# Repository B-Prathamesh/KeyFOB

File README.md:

# KeyFOB
Multipurpose keychain with Microcontroller

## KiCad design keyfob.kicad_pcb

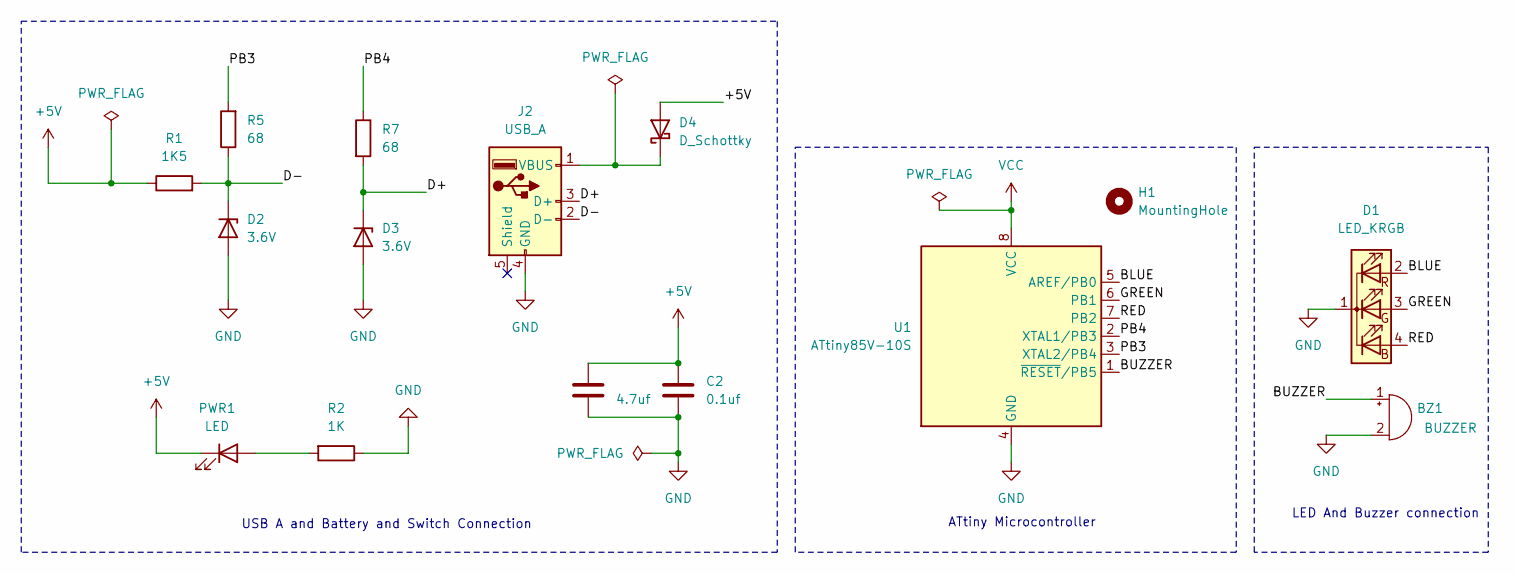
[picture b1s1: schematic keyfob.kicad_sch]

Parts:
BZ1: BUZZER; Buzzer_15x7.5RM7.6
C1: 4.7uf; C_Elec_3x5.4
C2: 0.1uf; C_Elec_3x5.4
D1: LED_KRGB; LED_RGB_1210
D2, D3: 3.6V; D_0805_2012Metric
D4: D_Schottky; D_0805_2012Metric
H1: MountingHole; MountingHole_4mm
J2: USB_A; USB_A_Molex_67643_Horizontal
PWR1: LED; LED_0805_2012Metric
R1: 1K5; R_0805_2012Metric
R2: 1K; R_0805_2012Metric
R5, R7: 68; R_0805_2012Metric
U1: ATtiny85V-10S; SOIC-8W_5.3x5.3mm_P1.27mm

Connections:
+5V: C1.1, C2.1, D4.2 (A), PWR1.1 (K), R1.1
/BLUE: D1.2 (RA), U1.5 (AREF/PB0)
/BUZZER: BZ1.1 (+), U1.1 (~RESET/PB5)
/D+: D3.1 (K), J2.3 (D+), R7.2
/D-: D2.1 (K), J2.2 (D-), R1.2, R5.1
/GREEN: D1.3 (GA), U1.6 (PB1)
/PB3: R5.2, U1.3 (XTAL2/PB4)
/PB4: R7.1, U1.2 (XTAL1/PB3)
/RED: D1.4 (BA), U1.7 (PB2)
GND: BZ1.2 (-), C1.2, C2.2, D1.1 (K), D2.2 (A), D3.2 (A), J2.4 (GND), R2.1, U1.4 (GND)
unnamed: D4.1 (K), J2.1 (VBUS)
unnamed: PWR1.2 (A), R2.2
VCC: U1.8 (VCC)

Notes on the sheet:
LED And Buzzer connection
USB A and Battery and Switch Connection
ATtiny Microcontroller

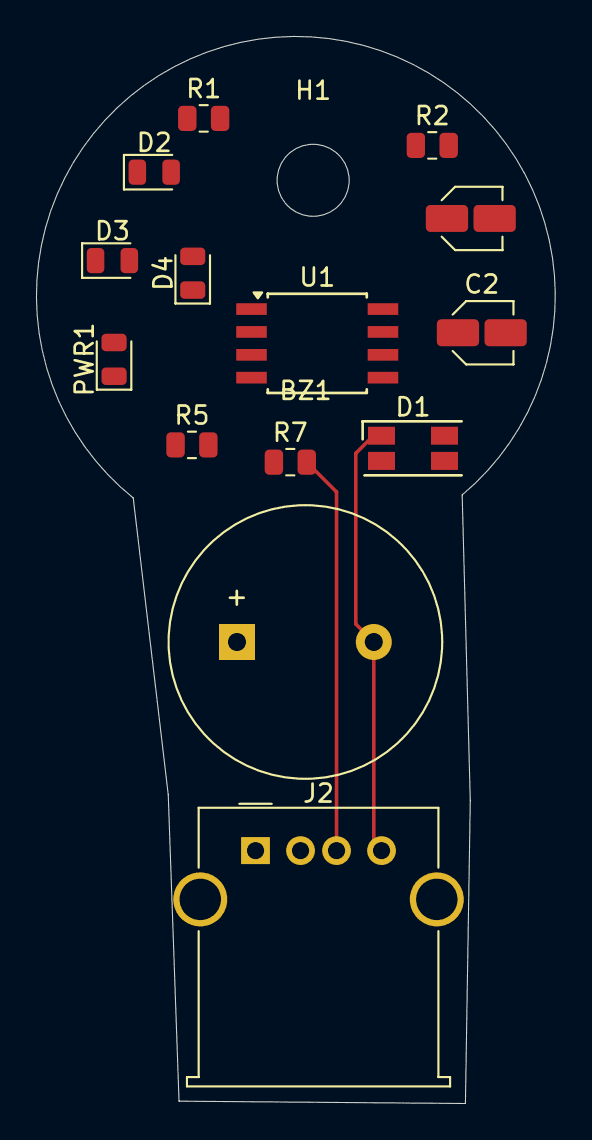
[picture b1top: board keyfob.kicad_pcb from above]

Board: 2 copper layers, 28.8 x 59.3 mm, 15 parts (0 on the bottom side), 12 nets.

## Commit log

2024-08-17 Uploading the initial project files
2024-08-17 Added the Data sheet
2024-08-19 Updated the Schematic Design
2024-08-22 Upadated the Schematic and PCB Design
2024-08-25 PCB layout done
